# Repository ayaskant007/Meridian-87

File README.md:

# Meridian 87

A tenkeyless mechanical keyboard with my own PCB, a Raspberry Pi Pico running QMK, and a rotary encoder where the Pause key would be. 85 soldered keys, a Tsangan-style bottom row with a 7u spacebar, screw-in stabilizers, and a 3D-printed case with a 7° typing angle.

## Why This Was Made

After building the Xeon Horizon macropad, I wanted to go all the way and design a full-size keyboard myself: the PCB, the plate, the case and the firmware, instead of buying one off the shelf.

## What It Does

- 85-key ANSI TKL layout with a Tsangan-style bottom row: 1.5u Ctrl, 1u Win, 1.5u Alt, 7u Space, 1.5u Alt, 1u Fn, 1.5u Ctrl
- Rotary encoder in the Pause slot: turn for volume, press to mute
- Hold Fn and the knob skips tracks; press it to play/pause
- Fn layer with media keys, screen brightness, Pause, a Win-key lock for gaming, an NKRO toggle and a bootloader shortcut
- Remap every key live in the browser with VIA, no recompiling
- N-key rollover over USB

## Firmware

**QMK, with the VIA keymap.** The RP2040 on the Pico is a first-class QMK target, QMK handles the 6×17 diode matrix and the EC11 encoder natively, and VIA lets you remap keys and the knob from a browser. There's no wireless, RGB or display on this board.

Prebuilt firmware is in [production/](production):

| File | Use it for |
| --- | --- |
| `meridian87_via.uf2` | Recommended. Remappable in VIA |
| `meridian87_default.uf2` | Fixed keymap, no VIA |

### Flashing

1. Hold the **BOOTSEL** button on the Pico and plug in the USB cable. A drive called `RPI-RP2` appears.
2. Drag `production/meridian87_via.uf2` onto it. The Pico reboots as a keyboard.

Once QMK is on the board you can skip the button: hold **Esc** while plugging in, or press **Fn + Esc**.

### Remapping with VIA

1. Open [usevia.app](https://usevia.app) in Chrome or Edge.
2. Go to Settings and turn on **Show Design tab**.
3. In Design, choose **Load Draft Definition** and pick [`FIRMWARE/meridian87_via.json`](FIRMWARE/meridian87_via.json).
4. Go to Configure and authorize the keyboard.

### Building From Source

1. Copy the `FIRMWARE` folder to `qmk_firmware/keyboards/meridian87`
2. Build:
   ```
   qmk compile -kb meridian87 -km via
   ```
   or `-km default` for the fixed keymap. The `.uf2` lands in the `qmk_firmware` folder.

If the knob skips or moves two steps per click, change `"resolution": 4` to `2` in `keyboard.json`. If volume goes the wrong way, swap `pin_a` and `pin_b`.

### Fn Layer

| Keys | Action |
| --- | --- |
| Fn + Esc | Bootloader (for flashing) |
| Fn + F1 / F2 | Screen brightness down / up |
| Fn + F5 / F6 / F7 / F8 | Previous / Play-Pause / Next / Stop |
| Fn + F9 / F10 / F11 | Mute / Volume down / Volume up |
| Fn + Scroll Lock | Pause |
| Fn + Win | Win-key lock |
| Fn + N | Toggle N-key rollover |
| Fn + turn knob | Previous / next track |
| Fn + press knob | Play / Pause |

## Pin Map

Raspberry Pi Pico, diodes COL2ROW (cathode toward the row).

| Signal | Pico GPIO |
| --- | --- |
| COL0 – COL16 | `GP0` – `GP16` |
| ROW0 – ROW5 | `GP17` – `GP22` |
| Encoder A | `GP27` |
| Encoder B | `GP26` |
| Encoder common | `GND` |
| Encoder push | Matrix row 0, column 16 |

## Case and Plate

The case is in `CAD/TKL_CASE.f3z` (Fusion) and `CAD/TKL_CASE.step`. Both are printed by Printing Legion.

- **Case bottom:** `Case_Bottom.step`, 400.12 × 150.9 × 36.4 mm, with 4 mm walls and a 7° typing angle.
- **Switch plate:** the `Plate_Reference` body, 400.12 × 150.9 × 1.5 mm. It sits on the case rim and is held with double-sided tape.
- **PCB:** hangs from the switches, 9 mm above the case floor. That leaves room for the diodes on the back.

## Bill of Materials

Prices were checked on 10 Nov 2026. USD is at ₹93.93 per dollar. Full links and notes are in [BOM.csv](BOM.csv).

| Name | Purpose | Qty | Cost (INR) | Cost (USD) | Distributor |
| --- | --- | ---: | ---: | ---: | --- |
| PCB, 2-layer, black, HASL (MOQ 5) | Main board | 5 | ₹2,630.04 | $28.00 | JLCPCB |
| PCB shipping (E-POST) | Delivery | 1 | ₹2,096.52 | $22.32 | JLCPCB |
| Raspberry Pi Pico | Microcontroller | 1 | ₹384.00 | $4.09 | Robu |
| 1x40 male header | Pico mounting | 2 | ₹16.00 | $0.17 | Robu |
| 1N4148 diode, DO-35 (onsemi) | Matrix diodes | 100 | ₹309.00 | $3.29 | Robu |
| EC11 encoder with switch, 20 mm | Volume knob | 1 | ₹58.00 | $0.62 | Robu |
| Knob, 15 mm | Encoder cap | 1 | ₹19.00 | $0.20 | Robu |
| Micro-USB data cable | Connect to PC | 1 | ₹49.00 | $0.52 | Robu |
| Outemu Peach v3 silent linear (10-pack) | Switches | 10 | ₹1,600.00 | $17.03 | Neomacro |
| Glorious GOAT screw-in stabilizers | 4 × 2u + 7u | 1 | ₹699.30 | $7.44 | Meckeys |
| Keychron Cherry PBT keycaps, Camel | Keycaps (incl. 7u + 1.5u mods) | 1 | ₹2,969.10 | $31.61 | Credkeys |
| Solder wire 60/40, 50 g | Consumable | 1 | ₹377.00 | $4.01 | Robu |
| Flux paste, 10 g | Consumable | 1 | ₹21.00 | $0.22 | Robu |
| Rubber bumper feet (100) | Anti-slip (optional) | 1 | ₹111.00 | $1.18 | Amazon.in |
| Case bottom + plate, 3D printed | Case | 1 | not priced | not priced | Printing Legion |
| Double-sided tape | Holds the plate | 1 | not priced | not priced | Self-sourced |

**Grand Total:** ₹11,338.96 ($120.72). This excludes the 3D prints, tape, and any customs duty on the PCB.

## Files

| Path | What's in it |
| --- | --- |
| `PCB/` | KiCad 9 project (schematic + PCB) |
| `production/gerbers.zip` | Gerbers + drill files for JLCPCB |
| `production/Meridian87_schematic.pdf` | Schematic |
| `production/*.uf2` | Ready-to-flash firmware |
| `FIRMWARE/` | QMK keyboard definition, keymaps and VIA definition |
| `CAD/` | Case, plate DXF and Fusion source |
| `images/` | PCB renders |

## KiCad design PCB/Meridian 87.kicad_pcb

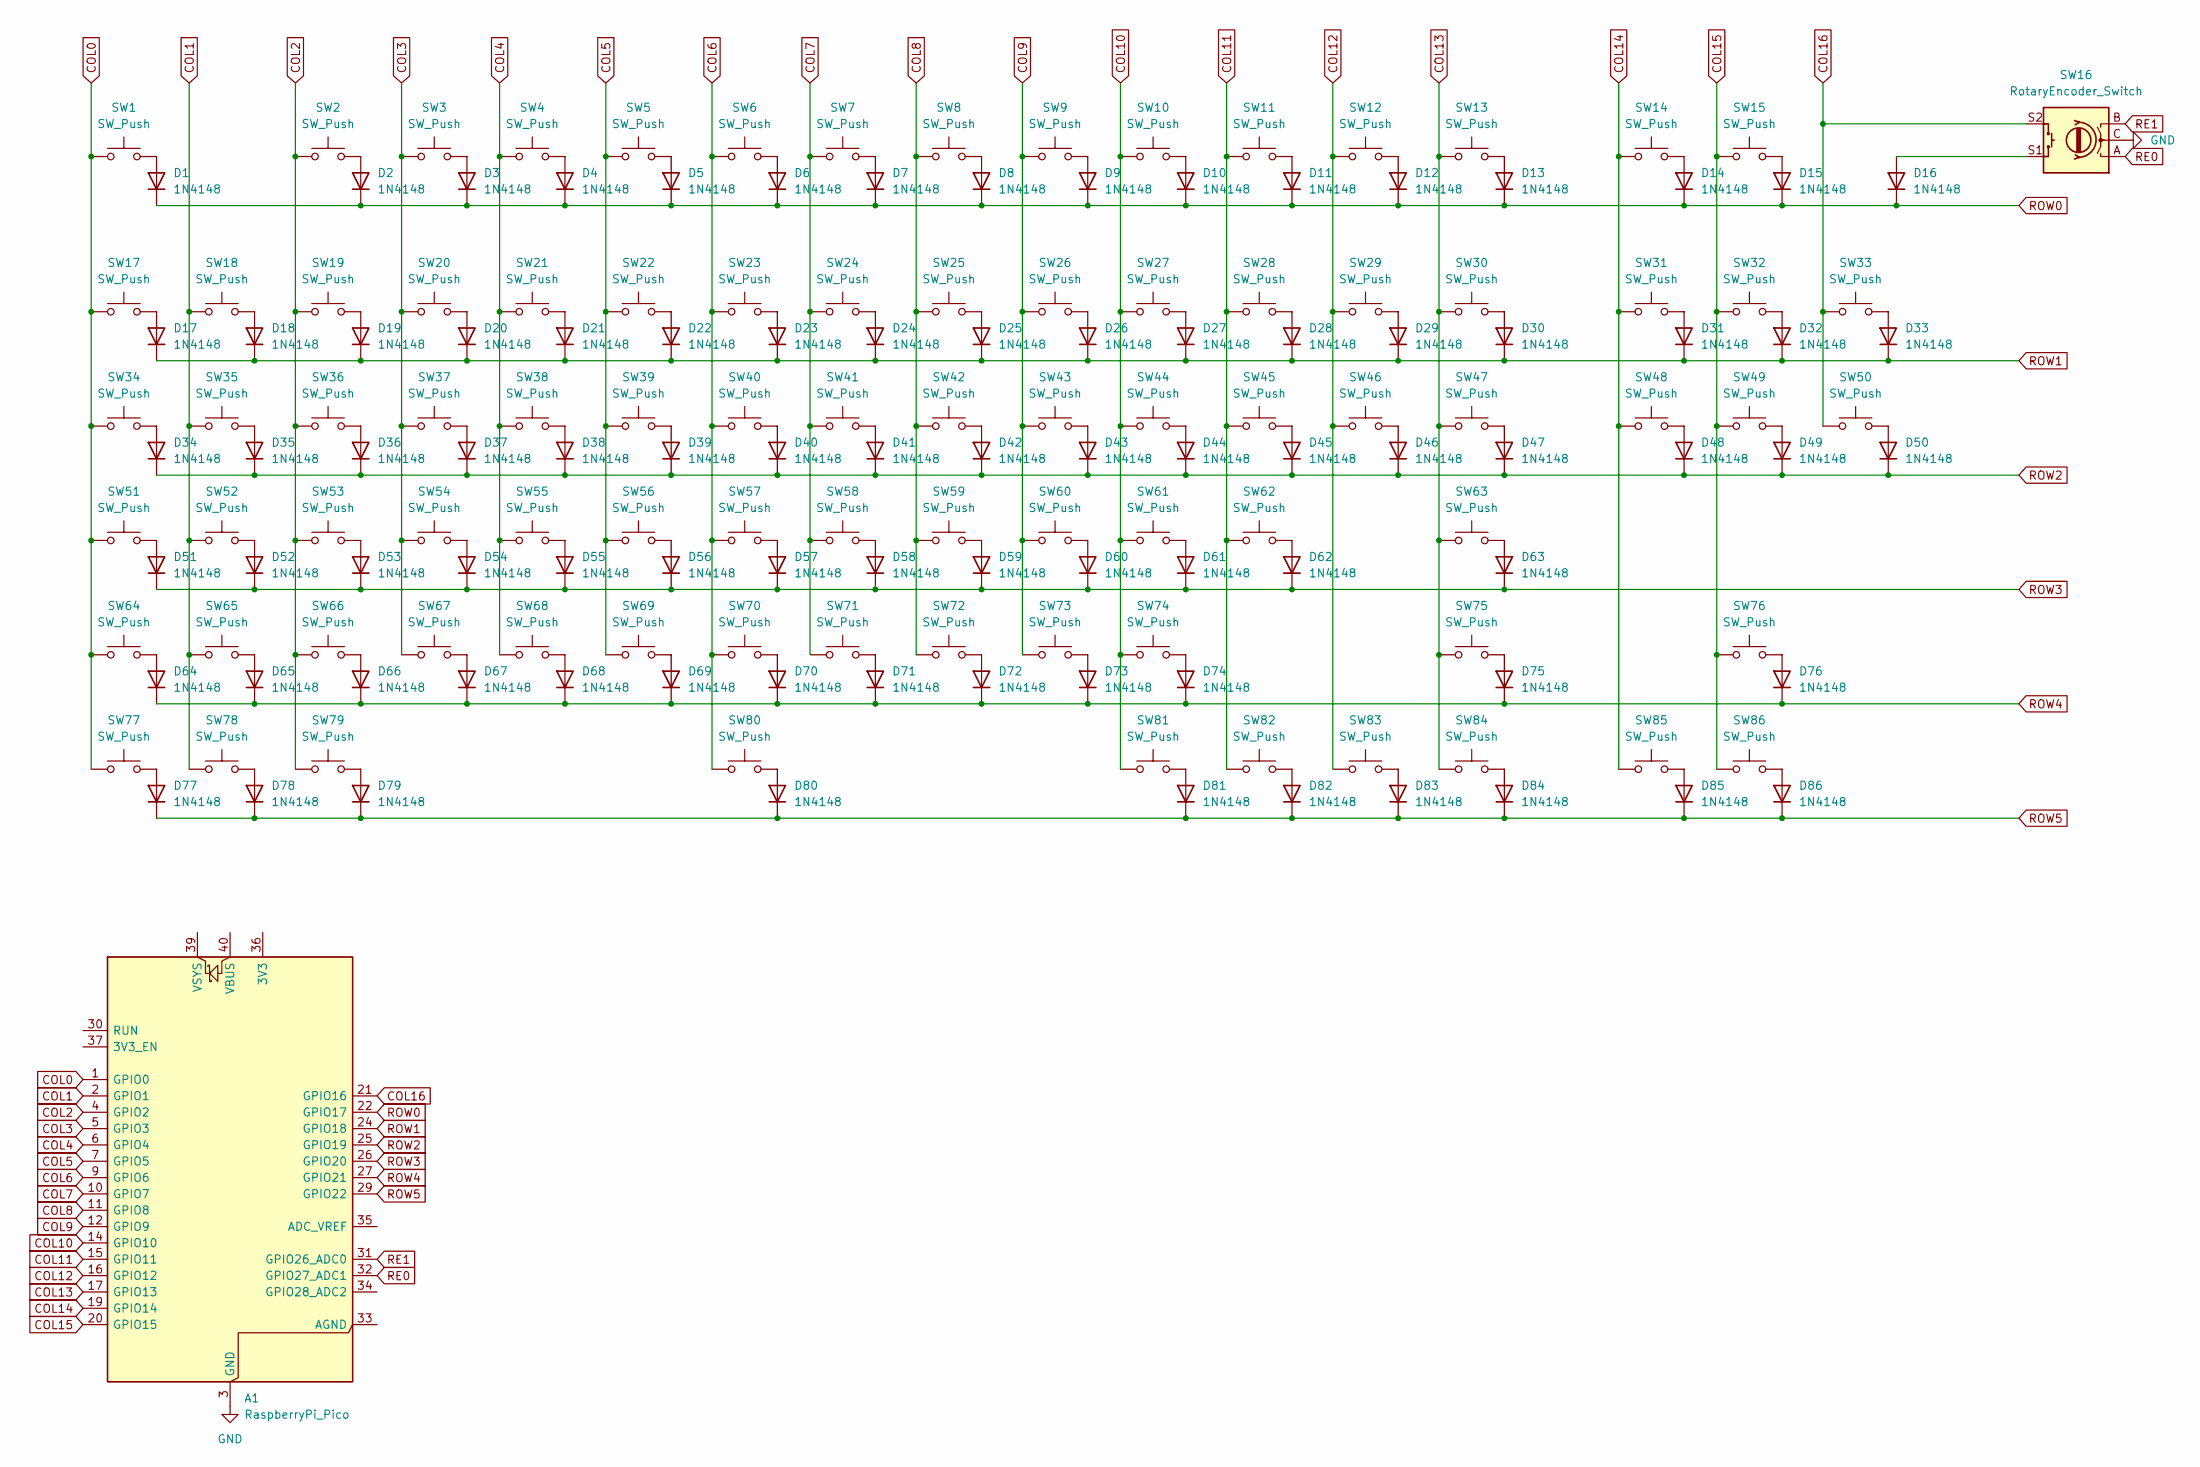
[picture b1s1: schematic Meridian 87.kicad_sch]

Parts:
A1: RaspberryPi_Pico; RaspberryPi_Pico_Common_THT
D1, D2, D3, D4, D5, D6, D7, D8, D9, D10, D11, D12, D13, D14, D15, D16, D17, D18, D19, D20, D21, D22, D23, D24, D25, D26, D27, D28, D29, D30, D31, D32, D33, D34, D35, D36, D37, D38, D39, D40, D41, D42, D43, D44, D45, D46, D47, D48, D49, D50, D51, D52, D53, D54, D55, D56, D57, D58, D59, D60, D61, D62, D63, D64, D65, D66, D67, D68, D69, D70, D71, D72, D73, D74, D75, D76, D77, D78, D79, D80, D81, D82, D83, D84, D85, D86: 1N4148; D_DO-35_SOD27_P7.62mm_Horizontal
SW1, SW2, SW3, SW4, SW5, SW6, SW7, SW8, SW9, SW10, SW11, SW12, SW13, SW14, SW15, SW17, SW18, SW19, SW20, SW21, SW22, SW23, SW24, SW25, SW26, SW27, SW28, SW29, SW31, SW32, SW33, SW35, SW36, SW37, SW38, SW39, SW40, SW41, SW42, SW43, SW44, SW45, SW46, SW48, SW49, SW50, SW52, SW53, SW54, SW55, SW56, SW57, SW58, SW59, SW60, SW61, SW62, SW65, SW66, SW67, SW68, SW69, SW70, SW71, SW72, SW73, SW74, SW76, SW85, SW86: SW_Push; SW_Cherry_MX_1.00u_PCB
SW16: RotaryEncoder_Switch; RotaryEncoder_Alps_EC11E-Switch_Vertical_H20mm
SW30: SW_Push; SW_Cherry_MX_2.00u_PCB
SW34, SW47: SW_Push; SW_Cherry_MX_1.50u_PCB
SW51: SW_Push; SW_Cherry_MX_1.75u_PCB
SW63, SW64: SW_Push; SW_Cherry_MX_2.25u_PCB
SW75: SW_Push; SW_Cherry_MX_2.75u_PCB
SW77, SW78, SW79, SW81, SW82, SW83, SW84: SW_Push; SW_Cherry_MX_1.25u_PCB
SW80: SW_Push; SW_Cherry_MX_PCB_7.00u

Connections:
COL0: A1.1 (GPIO0), SW1.1, SW17.1, SW34.1, SW51.1, SW64.1, SW77.1
COL1: A1.2 (GPIO1), SW18.1, SW35.2, SW52.1, SW65.1, SW78.1
COL2: A1.4 (GPIO2), SW2.1, SW19.1, SW36.1, SW53.1, SW66.1, SW79.1
COL3: A1.5 (GPIO3), SW3.1, SW20.1, SW37.1, SW54.1, SW67.1
COL4: A1.6 (GPIO4), SW4.1, SW21.1, SW38.1, SW55.1, SW68.1
COL5: A1.7 (GPIO5), SW5.1, SW22.1, SW39.1, SW56.1, SW69.1
COL6: A1.9 (GPIO6), SW6.1, SW23.1, SW40.1, SW57.1, SW70.1, SW80.1
COL7: A1.10 (GPIO7), SW7.1, SW24.1, SW41.1, SW58.1, SW71.1
COL8: A1.11 (GPIO8), SW8.1, SW25.1, SW42.1, SW59.1, SW72.1
COL9: A1.12 (GPIO9), SW9.1, SW26.1, SW43.1, SW60.1, SW73.1
COL10: A1.14 (GPIO10), SW10.1, SW27.1, SW44.1, SW61.1, SW74.1, SW81.1
COL11: A1.15 (GPIO11), SW11.1, SW28.1, SW45.1, SW62.1, SW82.1
COL12: A1.16 (GPIO12), SW12.1, SW29.1, SW46.1, SW83.1
COL13: A1.17 (GPIO13), SW13.1, SW30.1, SW47.1, SW63.1, SW75.1, SW84.1
COL14: A1.19 (GPIO14), SW14.1, SW31.1, SW48.1, SW85.1
COL15: A1.20 (GPIO15), SW15.1, SW32.1, SW49.1, SW76.1, SW86.1
COL16: A1.21 (GPIO16), SW16.S2, SW33.1, SW50.1
GND: A1.3 (GND), A1.8 (GND), A1.13 (GND), A1.18 (GND), A1.23 (GND), A1.28 (GND), A1.38 (GND), SW16.C
unnamed: D1.2 (A), SW1.2
unnamed: D2.2 (A), SW2.2
unnamed: D3.2 (A), SW3.2
unnamed: D4.2 (A), SW4.2
unnamed: D5.2 (A), SW5.2
unnamed: D6.2 (A), SW6.2
unnamed: D7.2 (A), SW7.2
unnamed: D8.2 (A), SW8.2
unnamed: D9.2 (A), SW9.2
unnamed: D10.2 (A), SW10.2
unnamed: D11.2 (A), SW11.2
unnamed: D12.2 (A), SW12.2
unnamed: D13.2 (A), SW13.2
unnamed: D14.2 (A), SW14.2
unnamed: D15.2 (A), SW15.2
unnamed: D16.2 (A), SW16.S1
unnamed: D17.2 (A), SW17.2
unnamed: D18.2 (A), SW18.2
unnamed: D19.2 (A), SW19.2
unnamed: D20.2 (A), SW20.2
unnamed: D21.2 (A), SW21.2
unnamed: D22.2 (A), SW22.2
unnamed: D23.2 (A), SW23.2
unnamed: D24.2 (A), SW24.2
unnamed: D25.2 (A), SW25.2
unnamed: D26.2 (A), SW26.2
unnamed: D27.2 (A), SW27.2
unnamed: D28.2 (A), SW28.2
unnamed: D29.2 (A), SW29.2
unnamed: D30.2 (A), SW30.2
unnamed: D31.2 (A), SW31.2
unnamed: D32.2 (A), SW32.2
unnamed: D33.2 (A), SW33.2
unnamed: D34.2 (A), SW34.2
unnamed: D35.2 (A), SW35.1
unnamed: D36.2 (A), SW36.2
unnamed: D37.2 (A), SW37.2
unnamed: D38.2 (A), SW38.2
unnamed: D39.2 (A), SW39.2
unnamed: D40.2 (A), SW40.2
unnamed: D41.2 (A), SW41.2
unnamed: D42.2 (A), SW42.2
unnamed: D43.2 (A), SW43.2
unnamed: D44.2 (A), SW44.2
unnamed: D45.2 (A), SW45.2
unnamed: D46.2 (A), SW46.2
unnamed: D47.2 (A), SW47.2
unnamed: D48.2 (A), SW48.2
unnamed: D49.2 (A), SW49.2
unnamed: D50.2 (A), SW50.2
unnamed: D51.2 (A), SW51.2
unnamed: D52.2 (A), SW52.2
unnamed: D53.2 (A), SW53.2
unnamed: D54.2 (A), SW54.2
unnamed: D55.2 (A), SW55.2
unnamed: D56.2 (A), SW56.2
unnamed: D57.2 (A), SW57.2
unnamed: D58.2 (A), SW58.2
unnamed: D59.2 (A), SW59.2
unnamed: D60.2 (A), SW60.2
unnamed: D61.2 (A), SW61.2
unnamed: D62.2 (A), SW62.2
unnamed: D63.2 (A), SW63.2
unnamed: D64.2 (A), SW64.2
unnamed: D65.2 (A), SW65.2
unnamed: D66.2 (A), SW66.2
unnamed: D67.2 (A), SW67.2
unnamed: D68.2 (A), SW68.2
unnamed: D69.2 (A), SW69.2
unnamed: D70.2 (A), SW70.2
unnamed: D71.2 (A), SW71.2
unnamed: D72.2 (A), SW72.2
unnamed: D73.2 (A), SW73.2
unnamed: D74.2 (A), SW74.2
unnamed: D75.2 (A), SW75.2
unnamed: D76.2 (A), SW76.2
unnamed: D77.2 (A), SW77.2
unnamed: D78.2 (A), SW78.2
unnamed: D79.2 (A), SW79.2
unnamed: D80.2 (A), SW80.2
unnamed: D81.2 (A), SW81.2
unnamed: D82.2 (A), SW82.2
unnamed: D83.2 (A), SW83.2
unnamed: D84.2 (A), SW84.2
unnamed: D85.2 (A), SW85.2
unnamed: D86.2 (A), SW86.2
RE0: A1.32 (GPIO27_ADC1), SW16.A
RE1: A1.31 (GPIO26_ADC0), SW16.B
ROW0: A1.22 (GPIO17), D1.1 (K), D2.1 (K), D3.1 (K), D4.1 (K), D5.1 (K), D6.1 (K), D7.1 (K), D8.1 (K), D9.1 (K), D10.1 (K), D11.1 (K), D12.1 (K), D13.1 (K), D14.1 (K), D15.1 (K), D16.1 (K)
ROW1: A1.24 (GPIO18), D17.1 (K), D18.1 (K), D19.1 (K), D20.1 (K), D21.1 (K), D22.1 (K), D23.1 (K), D24.1 (K), D25.1 (K), D26.1 (K), D27.1 (K), D28.1 (K), D29.1 (K), D30.1 (K), D31.1 (K), D32.1 (K), D33.1 (K)
ROW2: A1.25 (GPIO19), D34.1 (K), D35.1 (K), D36.1 (K), D37.1 (K), D38.1 (K), D39.1 (K), D40.1 (K), D41.1 (K), D42.1 (K), D43.1 (K), D44.1 (K), D45.1 (K), D46.1 (K), D47.1 (K), D48.1 (K), D49.1 (K), D50.1 (K)
ROW3: A1.26 (GPIO20), D51.1 (K), D52.1 (K), D53.1 (K), D54.1 (K), D55.1 (K), D56.1 (K), D57.1 (K), D58.1 (K), D59.1 (K), D60.1 (K), D61.1 (K), D62.1 (K), D63.1 (K)
ROW4: A1.27 (GPIO21), D64.1 (K), D65.1 (K), D66.1 (K), D67.1 (K), D68.1 (K), D69.1 (K), D70.1 (K), D71.1 (K), D72.1 (K), D73.1 (K), D74.1 (K), D75.1 (K), D76.1 (K)
ROW5: A1.29 (GPIO22), D77.1 (K), D78.1 (K), D79.1 (K), D80.1 (K), D81.1 (K), D82.1 (K), D83.1 (K), D84.1 (K), D85.1 (K), D86.1 (K)

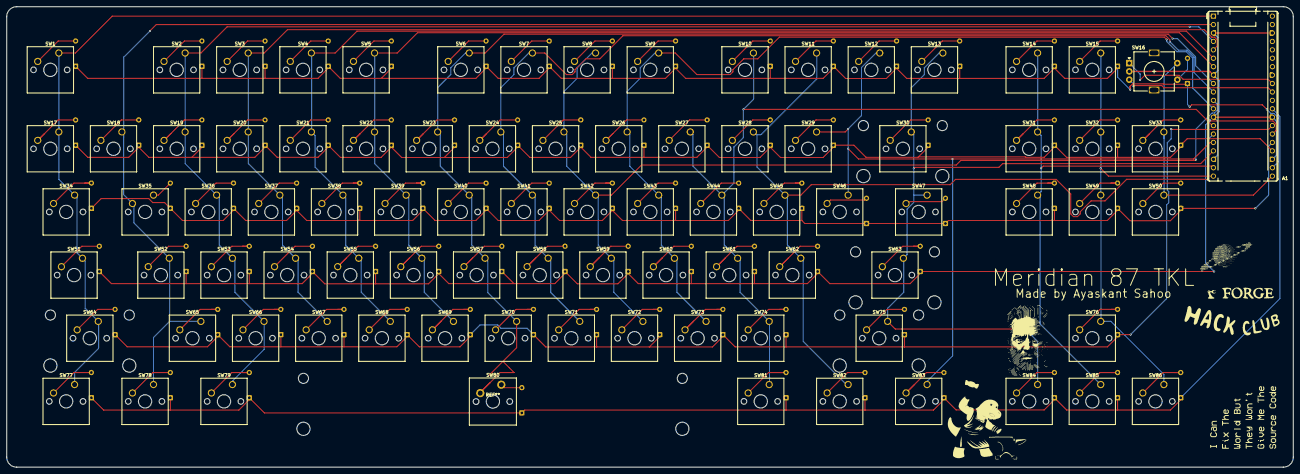
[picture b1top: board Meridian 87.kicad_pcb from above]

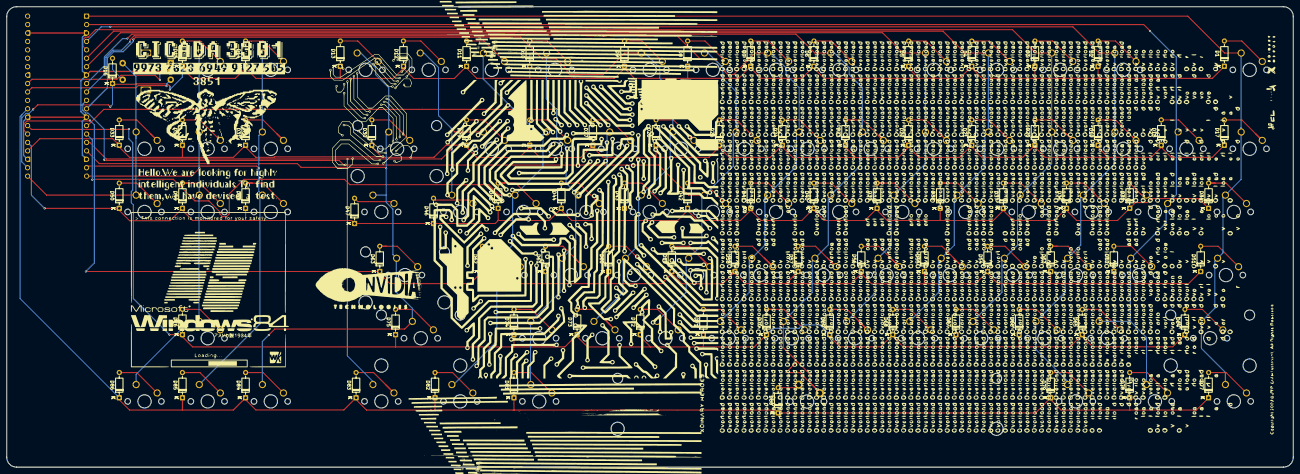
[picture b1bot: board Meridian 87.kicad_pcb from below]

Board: 2 copper layers, 388.1 x 138.9 mm, 173 parts (86 on the bottom side), 112 nets.

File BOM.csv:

Name,Purpose,Quantity,Total Cost (USD),Link,Distributor,Total Cost (INR),Notes
"PCB (2-layer, 1.6 mm FR4, black mask, HASL, 388.12 x 138.90 mm)","Main keyboard PCB; MOQ is 5, 1 used, 4 spare",5,28.00,https://cart.jlcpcb.com/quote,JLCPCB,2630.04,JLCONE desktop price (web price $30.00). Upload production/gerbers.zip. Checked 2026-11-10.
PCB shipping to India (E-POST),Delivery of the PCBs,1,22.32,https://cart.jlcpcb.com/quote,JLCPCB,2096.52,"10-18 business days, 1.06 kg. Any Indian customs duty charged on delivery is not included."
"Raspberry Pi Pico (original, without headers)",RP2040 microcontroller that runs QMK,1,4.09,https://robu.in/product/raspberry-pi-pico/,Robu,384.00,In stock. Footprint is Module:RaspberryPi_Pico_Common_THT.
"Male pin header 1x40, 2.54 mm",Solder the Pico to the PCB (break into 2 x 20),2,0.17,https://robu.in/product/1x40-berg-strip-male-connector/,Robu,16.00,Rs 8 each.
"1N4148 switching diode, DO-35 through-hole (onsemi)",One per key + encoder press for the 6x17 matrix (86 used),100,3.29,https://robu.in/product/1n4148-onsemi-100v-1v10ma-4ns-200ma-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,Robu,309.00,"Rs 3.09 each. Fits D_DO-35_SOD27_P7.62mm_Horizontal. Stripe (cathode) goes on the square pad, matching the silkscreen bar."
"EC11 rotary encoder with push switch, 20 mm knurled shaft (Hongyan EC11H 7CE20P1ZY20)",Volume knob in the Pause position,1,0.62,https://robu.in/product/hongyan-ec11h-7ce20p1zy20-rotary-enc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,Robu,58.00,"20 pulses / 20 detents (firmware resolution 4). 5 pins + 2 mounting tabs. Bare part, not a KY-040 module."
"Encoder knob, 15 mm OD, 6 mm knurled bore",Cap for the encoder,1,0.20,https://robu.in/product/potentiometer-knob-rotary-switch-cap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,Robu,19.00,Keep the knob 17 mm or smaller so it clears the Scroll Lock keycap.
"Micro-USB data cable, 1 m (USB-A to Micro-B)",Connects the keyboard to the PC,1,0.52,https://robu.in/product/micro-usb-a-to-micro-b-cable-120cm/,Robu,49.00,Data + power. The Pico has a Micro-USB port.
Outemu Peach v3 silent linear switches (pack of 10),"Key switches (85 used, 15 spare)",10,17.03,https://neomacro.in/products/outemu-peach-v3-silent,Neomacro,1600.00,"Rs 160 per pack. 40 g, factory lubed. Soldered build: PCB accepts 3-pin and 5-pin. Free shipping above Rs 1,500."
Glorious GOAT screw-in PCB stabilizers,"Stabilize Backspace 2u, Enter 2.25u, LShift 2.25u, RShift 2.75u and the 7u spacebar",1,7.44,https://meckeys.com/shop/accessories/keyboard-accessories/mo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,Meckeys,699.30,"Diwali price (regular Rs 999). Contains 5x 2U, 1x 6.25U, 1x 7U wires and 12 housings. Use 4x 2U + the 7U wire."
Keychron Cherry profile double-shot PBT full keycap set - Camel (219 keys),"Keycaps, including the Tsangan bottom row",1,31.61,https://credkeys.com/products/cherry-profile-double-shot-pbt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,Credkeys,2969.10,"Includes 2x 1.5U R1 Ctrl, 2x 1.5U R1 Alt, 1U R1 Win and Fn, and a 7U R1 spacebar. Tax included; shipping is calculated at checkout and is not included."
"Solder wire 60/40, 1.0 mm, 50 g (Noel)",Consumable for ~390 solder joints (skip if you have solder),1,4.01,https://robu.in/product/solder-wire-1-00mm-50gm/,Robu,377.00,Also keeps the Robu order above Rs 999 for free delivery.
"Flux paste, 10 g (Noel)",Consumable (skip if you have flux),1,0.22,https://robu.in/product/noel-flux-soldering-paste-10g/,Robu,21.00,
Clear self-adhesive rubber bumper feet (100 pcs),Anti-slip feet under the case (optional),1,1.18,https://www.amazon.in/dp/B0F7FKDTF9,Amazon.in,111.00,Free delivery as listed on 2026-11-10.
"Case bottom, 3D printed (CAD/Case_Bottom.step)",Case,1,,,Printing Legion,,Not priced (printed by Printing Legion). 400.12 x 150.9 x 36.4 mm; needs a 400 mm bed or a split print. See README for required fixes before printing.
"Switch plate, 3D printed, 1.5 mm (Plate_Reference body in CAD/TKL_CASE.step)",Holds the switches; sits on the case rim,1,,,Printing Legion,,Not priced (printed by Printing Legion). Must be exactly 1.5 mm thick. Case_Top.step is empty; export the Plate_Reference body instead.
Double-sided tape (VHB),Holds the plate on the case rim,1,,,Self-sourced,,Not priced (sourced by you).
"Shipping - Robu, Meckeys, Neomacro",,,0.00,,,0.00,"Robu free above Rs 999 (order is Rs 1,233); Meckeys free shipping; Neomacro free above Rs 1,500."
Shipping - Credkeys,,,,,,,Calculated at checkout; not included.
"TOTAL (excl. 3D prints, tape, Credkeys shipping, customs)",,,120.72,,,11338.96,"USD at Rs 93.93/USD (open.er-api.com, 2026-11-10)"

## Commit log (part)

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2026-06-04 Made & Added PCB and some footprints
2026-06-04 Added new MCU SYMBOLS & FOOTPRINTS
